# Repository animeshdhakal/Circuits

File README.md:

# Circuits
Circuits built my me

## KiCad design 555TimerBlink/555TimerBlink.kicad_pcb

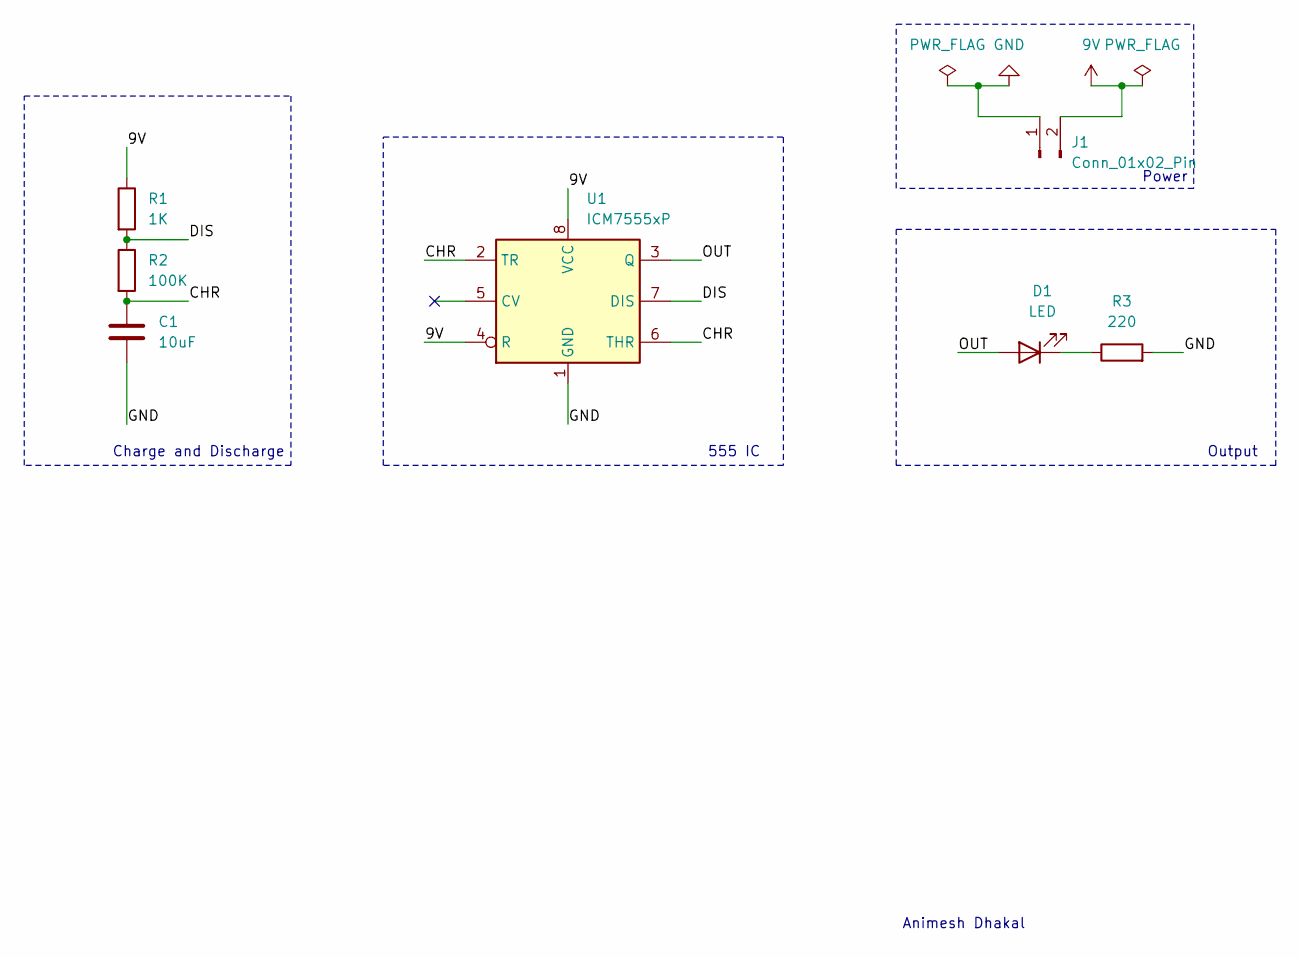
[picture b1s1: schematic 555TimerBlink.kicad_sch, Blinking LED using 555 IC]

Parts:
C1: 10uF; C_Radial_D5.0mm_H7.0mm_P2.00mm
D1: LED; LED_D3.0mm
J1: Conn_01x02_Pin; PinHeader_1x02_P2.54mm_Vertical
R1: 1K; Resistor_small
R2: 100K; Resistor_small
R3: 220; Resistor_small
U1: ICM7555xP; DIP-8_W7.62mm

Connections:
9V: J1.2, R1.1, U1.4 (R), U1.8 (VCC)
/CHR: C1.1, R2.2, U1.2 (TR), U1.6 (THR)
/DIS: R1.2, R2.1, U1.7 (DIS)
/OUT: D1.2 (A), U1.3 (Q)
GND: C1.2, J1.1, R3.2, U1.1 (GND)
unnamed: D1.1 (K), R3.1

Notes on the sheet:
Power
555 IC
Animesh Dhakal
Output
Charge and Discharge

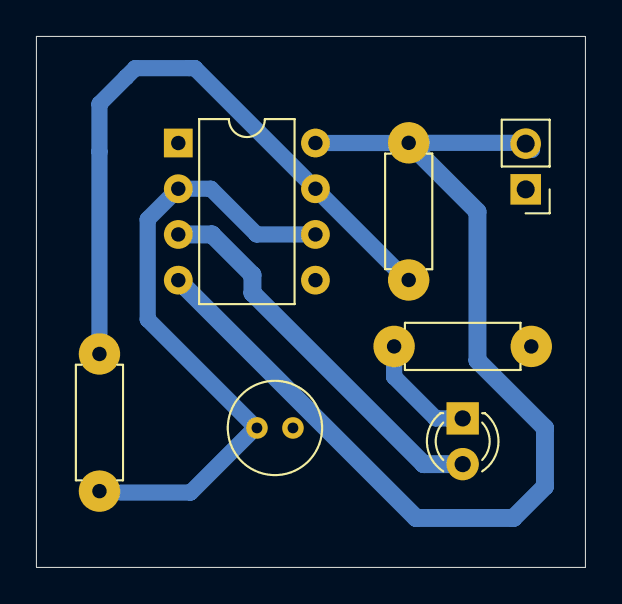
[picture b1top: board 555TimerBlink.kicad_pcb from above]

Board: 2 copper layers, 30.5 x 29.5 mm, 7 parts (0 on the bottom side), 6 nets.

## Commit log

2024-11-22 Added 555Timer Blink Circuit
